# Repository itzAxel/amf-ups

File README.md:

# AMF: "A Modem's Fellow"

A simple uninterruptible power supply (UPS) project for low-voltage appliances.

## Specifications

| Parameter | Minimum | Nominal | Maximum | Notes |
| :--- | :---: | :---: | :---: | :--- |
| Input Voltage | 9V | 12V | 15V | None |
| Output Voltage | 9V | 12V | 12.6V | Step-up output voltage can be regulated by changing `R2`/`R3` |

* **Charger IC:** [TP5100](https://cdn.hackaday.io/files/1948598336847456/TP5100-ENG.pdf)
* **Main Step-Up Converter:** [TPS61088](https://www.ti.com/lit/ds/symlink/tps61088-q1.pdf)

### Absolute Maximum Ratings

| Rating | Limit | Notes |
| :--- | :---: | :--- |
| Input Voltage | 20V | See Note 1 |
| Output Voltage | 14.5V | See Note 2 |
| Output Current | 3A | None |
| Battery Current | 10A | None |

> **Warning:** Stresses beyond those listed under Absolute Maximum Ratings may cause permanent damage to the device.

> **Battery Protection Notice:** This board does not include integrated cell balancing or over-discharge protection. Any connected 2S Li-Ion battery pack **must** have a proper Battery Management System (BMS) with cell balancing and protection circuitry. Operating an unprotected pack risks overcharging, over-discharging, permanent cell damage, or fire.

> **NTC Thermistor Notice:** Connect an NTC thermistor for thermal monitoring. If an NTC thermistor is not used, short the NTC connection with a 0-ohm resistor (or a piece of wire). It is also recommended to desolder `R8`.

**Note 1:** Supplying voltage higher than 20V may cause:
1. Permanent MOSFET (`AO3407A`) gate oxide layer damage
2. Permanent damage to the charger IC (`TP5100`)
3. **Potential life-threatening fire and/or explosion of the connected Li-Ion battery**

**Note 2:** Supplying voltage into the *Output* connector may cause a backpowering event, which can lead to:
1. Permanent MOSFET (`AO3407A`) gate oxide layer damage
2. Permanent damage to the step-up converter (`TPS61088`)
3. **Potential life-threatening fire and/or explosion of the connected Li-Ion battery**

## Current Features

1. Automatic switchover (**NIPM™**) to the battery if the input voltage drops near 0V.
2. Dedicated 8.4V (2S) pack charger (`TP5100`, 1A) — *requires an external BMS with cell balancing on the battery pack*.
3. Charging indication.

## TODO

1. Better switchover circuitry with a proper `Vref`.
2. 1.27mm I/O header to communicate with an MCU.

## NIPM™: "Not Intellectual Power Manager"

### Operation Description

* **When 12V input is present:**
  * The P-channel MOSFET (`AO3407A`) is OFF, isolating the `TPS61088` from the output.
  * The diode (`SS34`) is forward-biased, allowing current to pass almost directly from the 12V input jack to the load.

* **When 12V input is missing:**
  * The P-channel MOSFET gate is pulled down by `R1` (10kΩ), connecting the battery path to the load.
  * The diode is reverse-biased, blocking current from leaking back into the 12V input line.

## Misc
* **Images of the PCB sit at `/Images/`**
* **You can have a look at the schematic, it's in `Schematic.pdf` file**

## Legal

This project is published under the MIT License. See the `LICENSE` file for the full license notice.

Fonts, footprints, symbols, and other third-party files are published under their respective licenses.

THE PROJECT IS PROVIDED "AS-IS", WITHOUT WARRANTY OF ANY KIND, EXPRESS OR IMPLIED, INCLUDING BUT NOT LIMITED TO THE WARRANTIES OF MERCHANTABILITY, FITNESS FOR A PARTICULAR PURPOSE AND NONINFRINGEMENT.

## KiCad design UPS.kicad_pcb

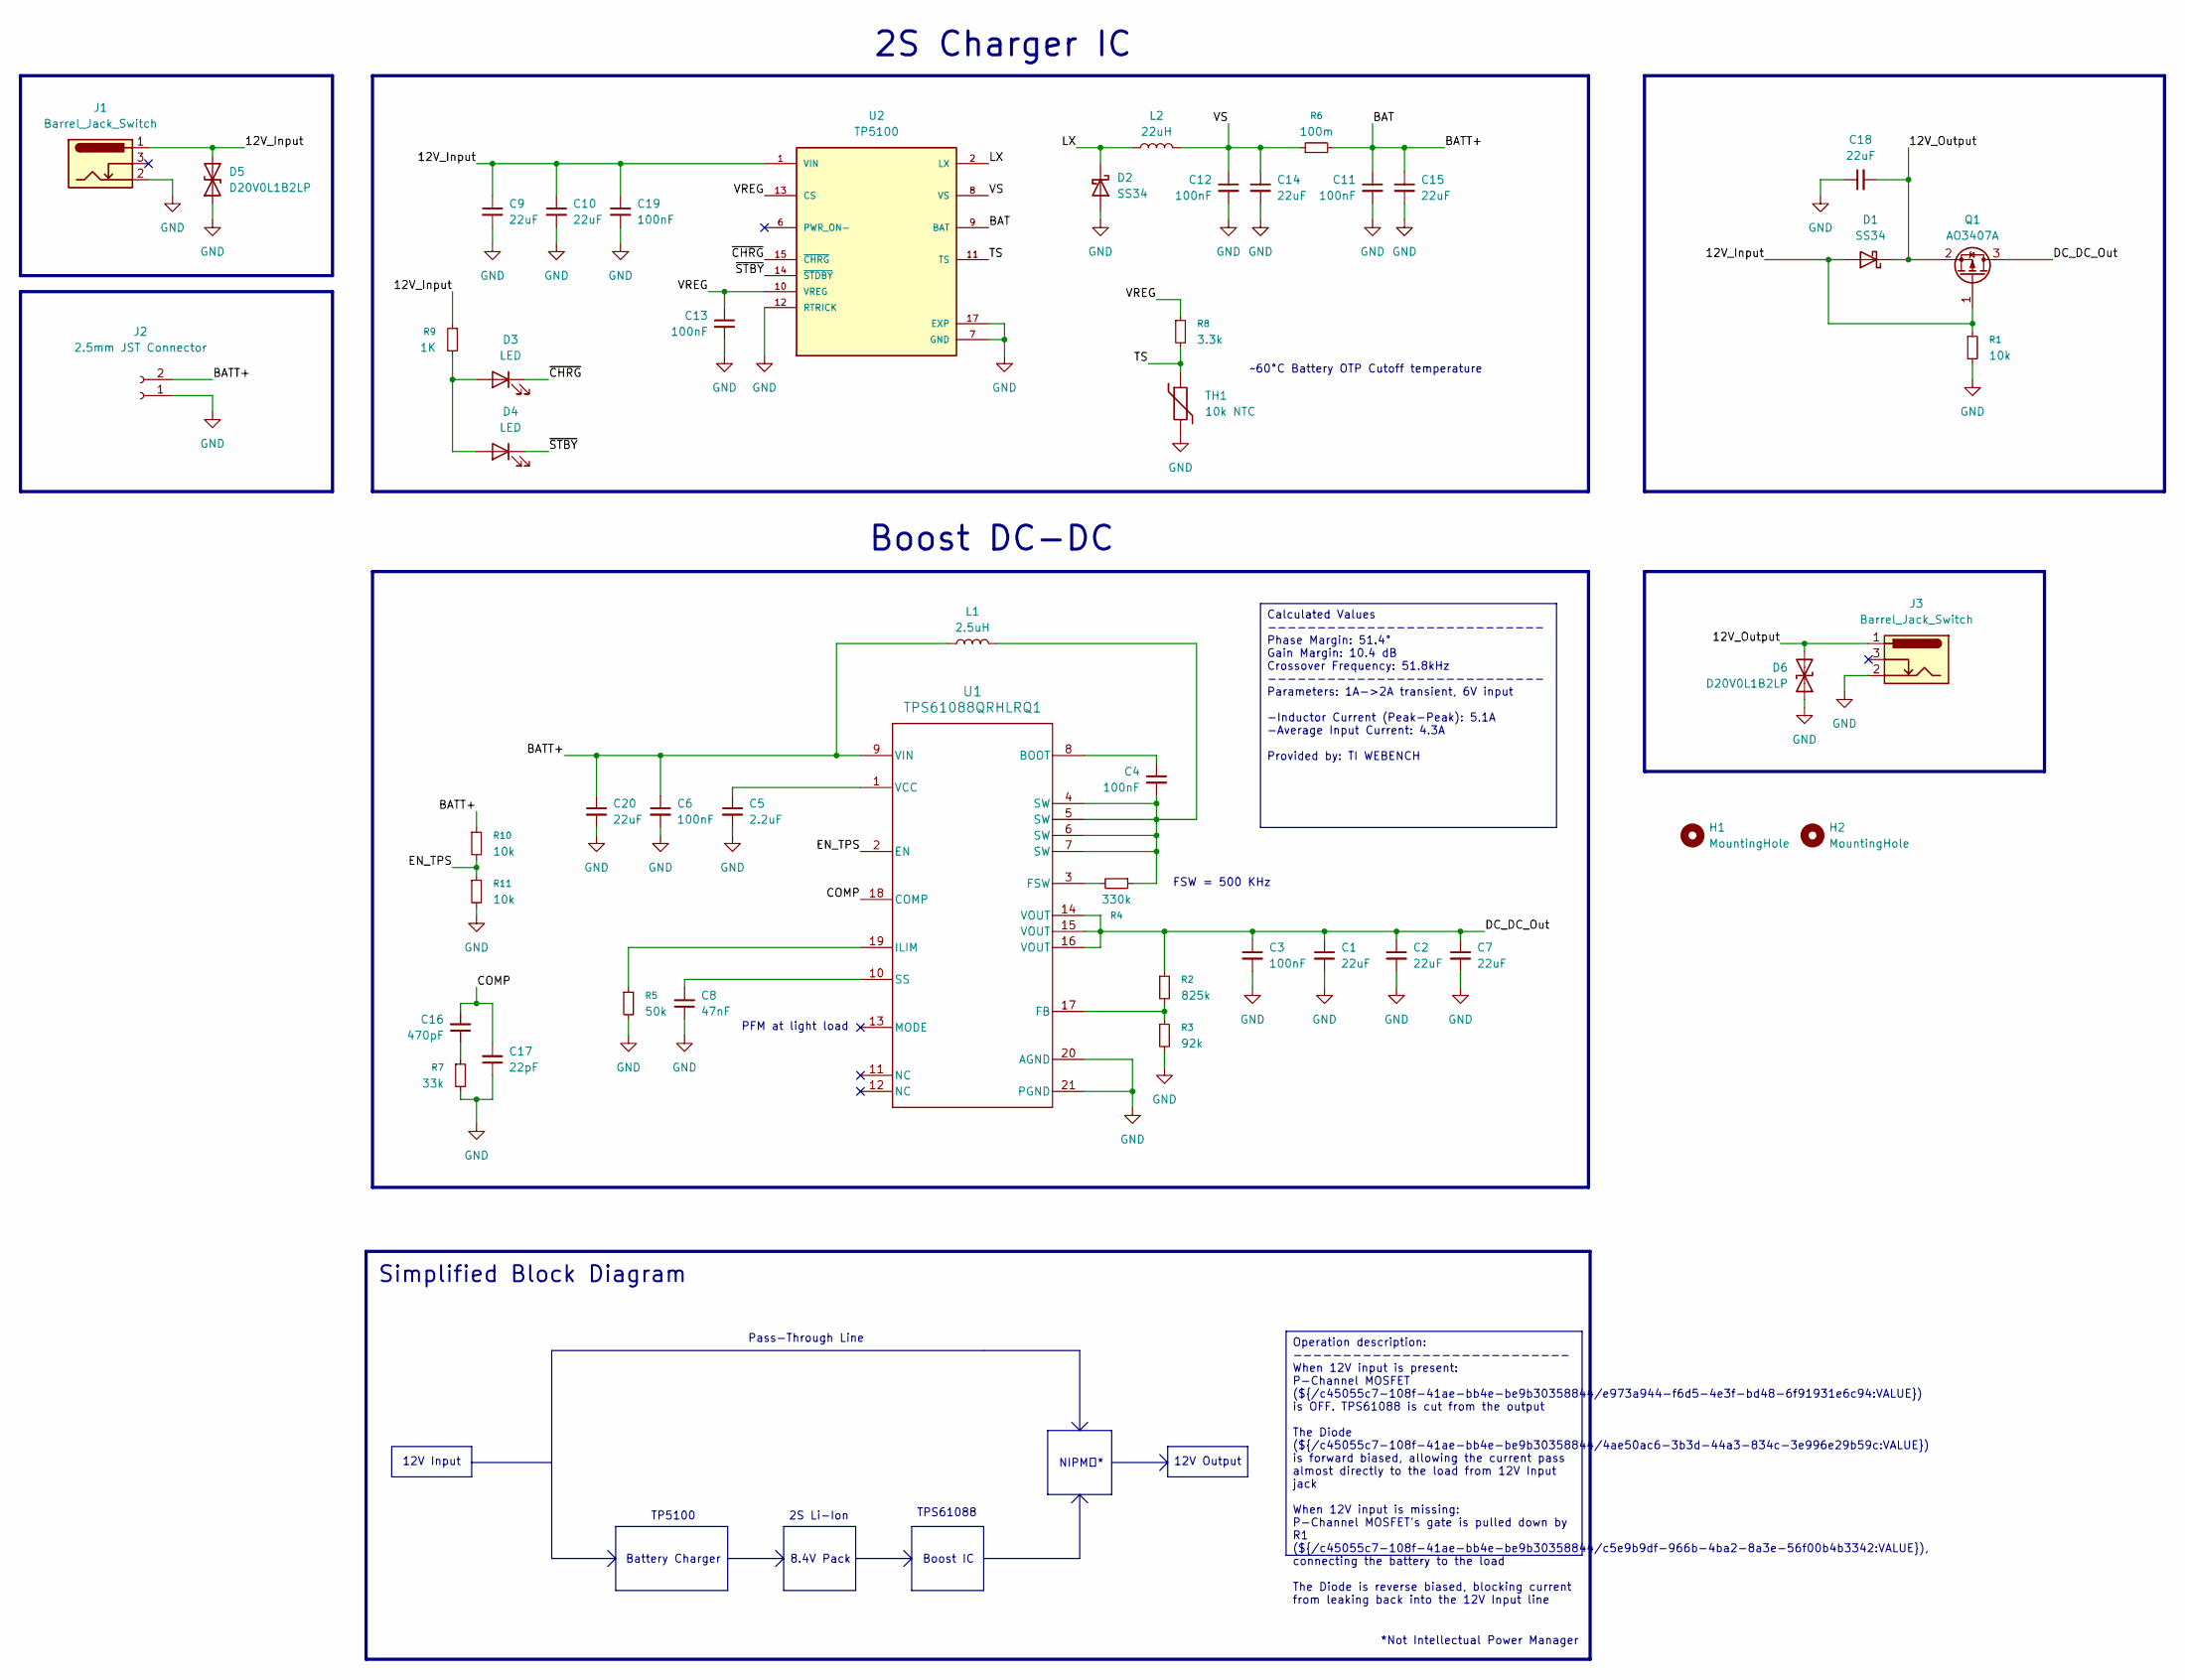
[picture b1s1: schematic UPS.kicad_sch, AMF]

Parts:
C1, C2, C7, C9, C10, C14, C15, C18, C20: 22uF; C_1206_3216Metric
C3, C4, C6, C11, C12, C13, C19: 100nF; C_0603_1608Metric
C5: 2.2uF; C_1206_3216Metric
C8: 47nF; C_0603_1608Metric
C16: 470pF; C_0402_1005Metric
C17: 22pF; C_0402_1005Metric
D1, D2: SS34; D_SMA
D3, D4: LED; LED_0603_1608Metric
D5, D6: D20V0L1B2LP; D_0402_1005Metric
H1, H2: MountingHole; MountingHole_2.2mm_M2
J1, J3: Barrel_Jack_Switch; BarrelJack_GCT_DCJ200-10-A_Horizontal
J2: 2.5mm JST Connector; JST_XH_S2B-XH-A-1_1x02_P2.50mm_Horizontal
L1: 2.5uH; L_Vishay_IHLP-2525
L2: 22uH; L_Wurth_WE-MAPI-5020
Q1: AO3407A; SOT-23
R1, R10, R11: 10k; R_0402_1005Metric
R2: 825k; R_0603_1608Metric
R3: 92k; R_0603_1608Metric
R4: 330k; R_0402_1005Metric
R5: 50k; R_0402_1005Metric
R6: 100m; R_1206_3216Metric
R7: 33k; R_0402_1005Metric
R8: 3.3k; R_0402_1005Metric
R9: 1K; R_0603_1608Metric
TH1: 10k NTC; PinHeader_1x02_P2.54mm_Vertical
U1: TPS61088QRHLRQ1; RHL0020A
U2: TP5100; NXP_VQFN-16-1EP_4x4mm_P0.65mm_EP2.1x2.1mm; MPN TP5100

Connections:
/12V_Input: C9.1, C10.1, C19.1, D1.2 (A), D5.2 (A2), J1.1, Q1.1 (G), R1.1, R9.1, U2.1 (VIN), U2.4 (VIN), U2.5 (VIN), U2.16 (VIN)
/12V_Output: C18.2, D1.1 (K), D6.2 (A2), J3.1, Q1.2 (S)
/BAT: C6.1, C11.1, C15.1, C20.1, J2.2, L1.1, R6.2, R10.1, U1.9 (VIN), U2.9 (BAT)
/COMP: C16.2, C17.2, U1.18 (COMP)
/DC_DC_Out: C1.1, C2.1, C3.1, C7.1, Q1.3 (D), R2.1, U1.14 (VOUT), U1.15 (VOUT), U1.16 (VOUT)
/EN_TPS: R10.2, R11.1, U1.2 (EN)
/LX: D2.1 (K), L2.1, U2.2 (LX), U2.3 (LX)
/TS: R8.2, TH1.1, U2.11 (TS)
/VREG: C13.1, R8.1, U2.10 (VREG), U2.13 (CS)
/VS: C12.1, C14.1, L2.2, R6.1, U2.8 (VS)
/~CHRG: D3.1 (K), U2.15 (~CHRG)
/~STBY: D4.1 (K), U2.14 (~STDBY)
GND: C1.2, C2.2, C3.2, C5.2, C6.2, C7.2, C8.1, C9.2, C10.2, C11.2, C12.2, C13.2, C14.2, C15.2, C17.1, C18.1, C19.2, C20.2, D2.2 (A), D5.1 (A1), D6.1 (A1), J1.2, J2.1, J3.2, R1.2, R3.2, R5.2, R7.2, R11.2, TH1.2, U1.20 (AGND), U1.21 (PGND), U2.7 (GND), U2.12 (RTRICK), U2.17 (EXP)
unnamed: C4.2, L1.2, R4.1, U1.4 (SW), U1.5 (SW), U1.6 (SW), U1.7 (SW)
unnamed: C16.1, R7.1
unnamed: D3.2 (A), D4.2 (A), R9.2
unnamed: C4.1, U1.8 (BOOT)
unnamed: R2.2, R3.1, U1.17 (FB)
unnamed: R4.2, U1.3 (FSW)
unnamed: R5.1, U1.19 (ILIM)
unnamed: C8.2, U1.10 (SS)
unnamed: C5.1, U1.1 (VCC)

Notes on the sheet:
PFM at light load
*Not Intellectual Power Manager
2S Li-Ion
Pass-Through Line
2S Charger IC
Boost IC
12V Input
12V Output
TP5100
8.4V Pack
Boost DC-DC
NIPM™*
FSW = 500 KHz
TPS61088
Battery Charger
Simplified Block Diagram
~60°C Battery OTP Cutoff temperature
Operation description: ---------------------------- When 12V input is present: P-Channel MOSFET (${/c45055c7-108f-41ae-bb4e-be9b30358844/e973a944-f6d5-4e3f-bd48-6f91931e6c94:VALUE}) is OFF. TPS61088 is cut from the output The Diode (${/c45055c7-108f-41ae-bb4e-be9b30358844/4ae50ac6-3b3d-44a3-834c-3e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
Calculated Values ---------------------------- Phase Margin: 51.4° Gain Margin: 10.4 dB Crossover Frequency: 51.8kHz ---------------------------- Parameters: 1A->2A transient, 6V input -Inductor Current (Peak-Peak): 5.1A -Average Input Current: 4.3A Provided by: TI WEBENCH

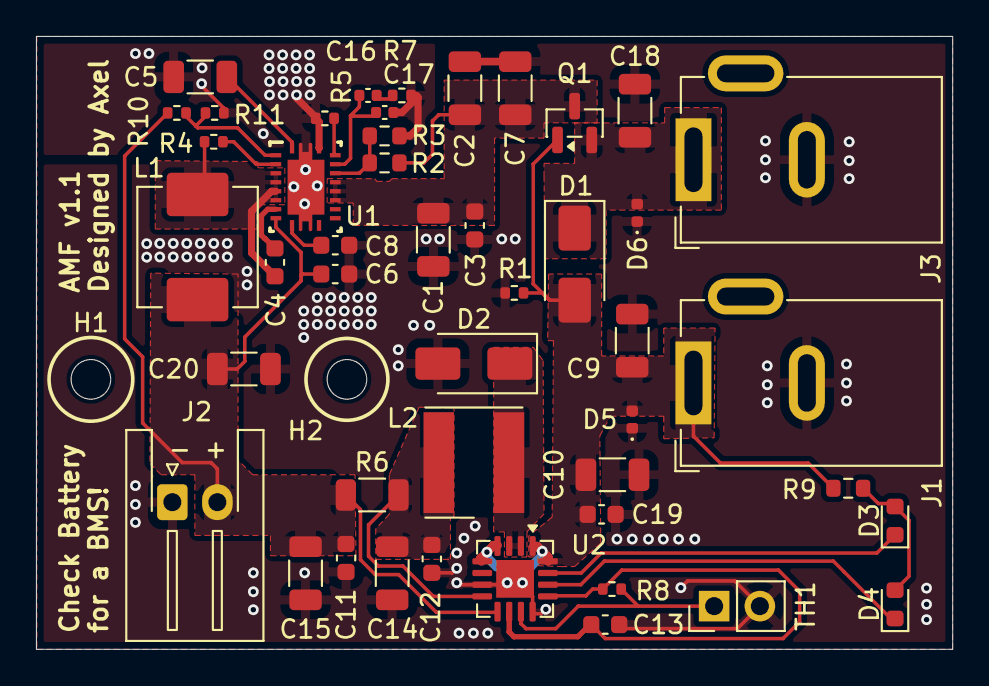
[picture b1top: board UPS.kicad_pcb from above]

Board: 2 copper layers, 50.9 x 34.1 mm, 48 parts (0 on the bottom side), 22 nets.
